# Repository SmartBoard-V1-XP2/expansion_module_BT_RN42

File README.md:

# Expansion Module: Bluetooth RN42-I/RM

## Overview
This repository hosts the design and implementation of the Bluetooth RN42-I/RM Expansion Module. The RN42 is a small form factor, low power Bluetooth 2.1 + EDR module designed for adding robust wireless capability to any device. It is perfect for mobile applications and is fully compliant with Bluetooth 2.1 + EDR standards. The module can easily be connected to a microcontroller or a processor board for Bluetooth serial communication via UART.

## Key Features of RN42
- **Bluetooth 2.1 + EDR**: Ensures compatibility with a wide range of devices and offers enhanced data rate (EDR) for faster data transfer.
- **Low Power Consumption**: Ideal for battery-powered applications with its low power consumption in sleep mode.
- **Class 2 Transmission**: Offers a reliable wireless range of up to 30 meters.
- **Easy Integration**: Supports multiple interfaces including UART, GPIOs which makes it versatile for integration into different projects.
- **Compact Size**: The module's small footprint (26.92mm x 13.21mm x 2.0mm) makes it suitable for space-constrained applications.

For more detailed information on the RN42 module, including technical specifications and usage guidelines, please refer to the [RN42 Datasheet](RN42_50002328A.pdf) available in this repository.

## Module Overview
The RN42-I/RM module is engineered for rapid integration into devices requiring wireless connectivity. It provides a high-speed interface between the device and its intended application, with minimal power consumption and robust connectivity features. The module supports secure and encrypted data transmission, ensuring that your device communicates safely over Bluetooth connections.

## Contributions and Feedback
Contributions to this project are welcome. If you have suggestions for improvement or have developed additional features, please fork the repository, make your changes, and submit a pull request. For any questions or issues, please open an issue in the GitHub repository.

## License
This project is licensed under the MIT License with the following terms:

- **Permission to Use**: You are free to use, modify, and distribute this design in both private and commercial settings.
- **Attribution Requirement**: While not required, attribution to the original author, Adam Łuczak, is appreciated. This can be done through a citation or a link back to this repository.
- **No Warranty**: This design is provided "as is", without warranty of any kind. Use it at your own risk.
- **Liability**: The author is not liable for any damages or losses that may arise from the use of this design.

For the full terms and conditions, please refer to the MIT License documentation.

## Contact
Should you have any inquiries or suggestions regarding this project, please don't hesitate to contact Adam Łuczak at adam.luczak@outlook.com.

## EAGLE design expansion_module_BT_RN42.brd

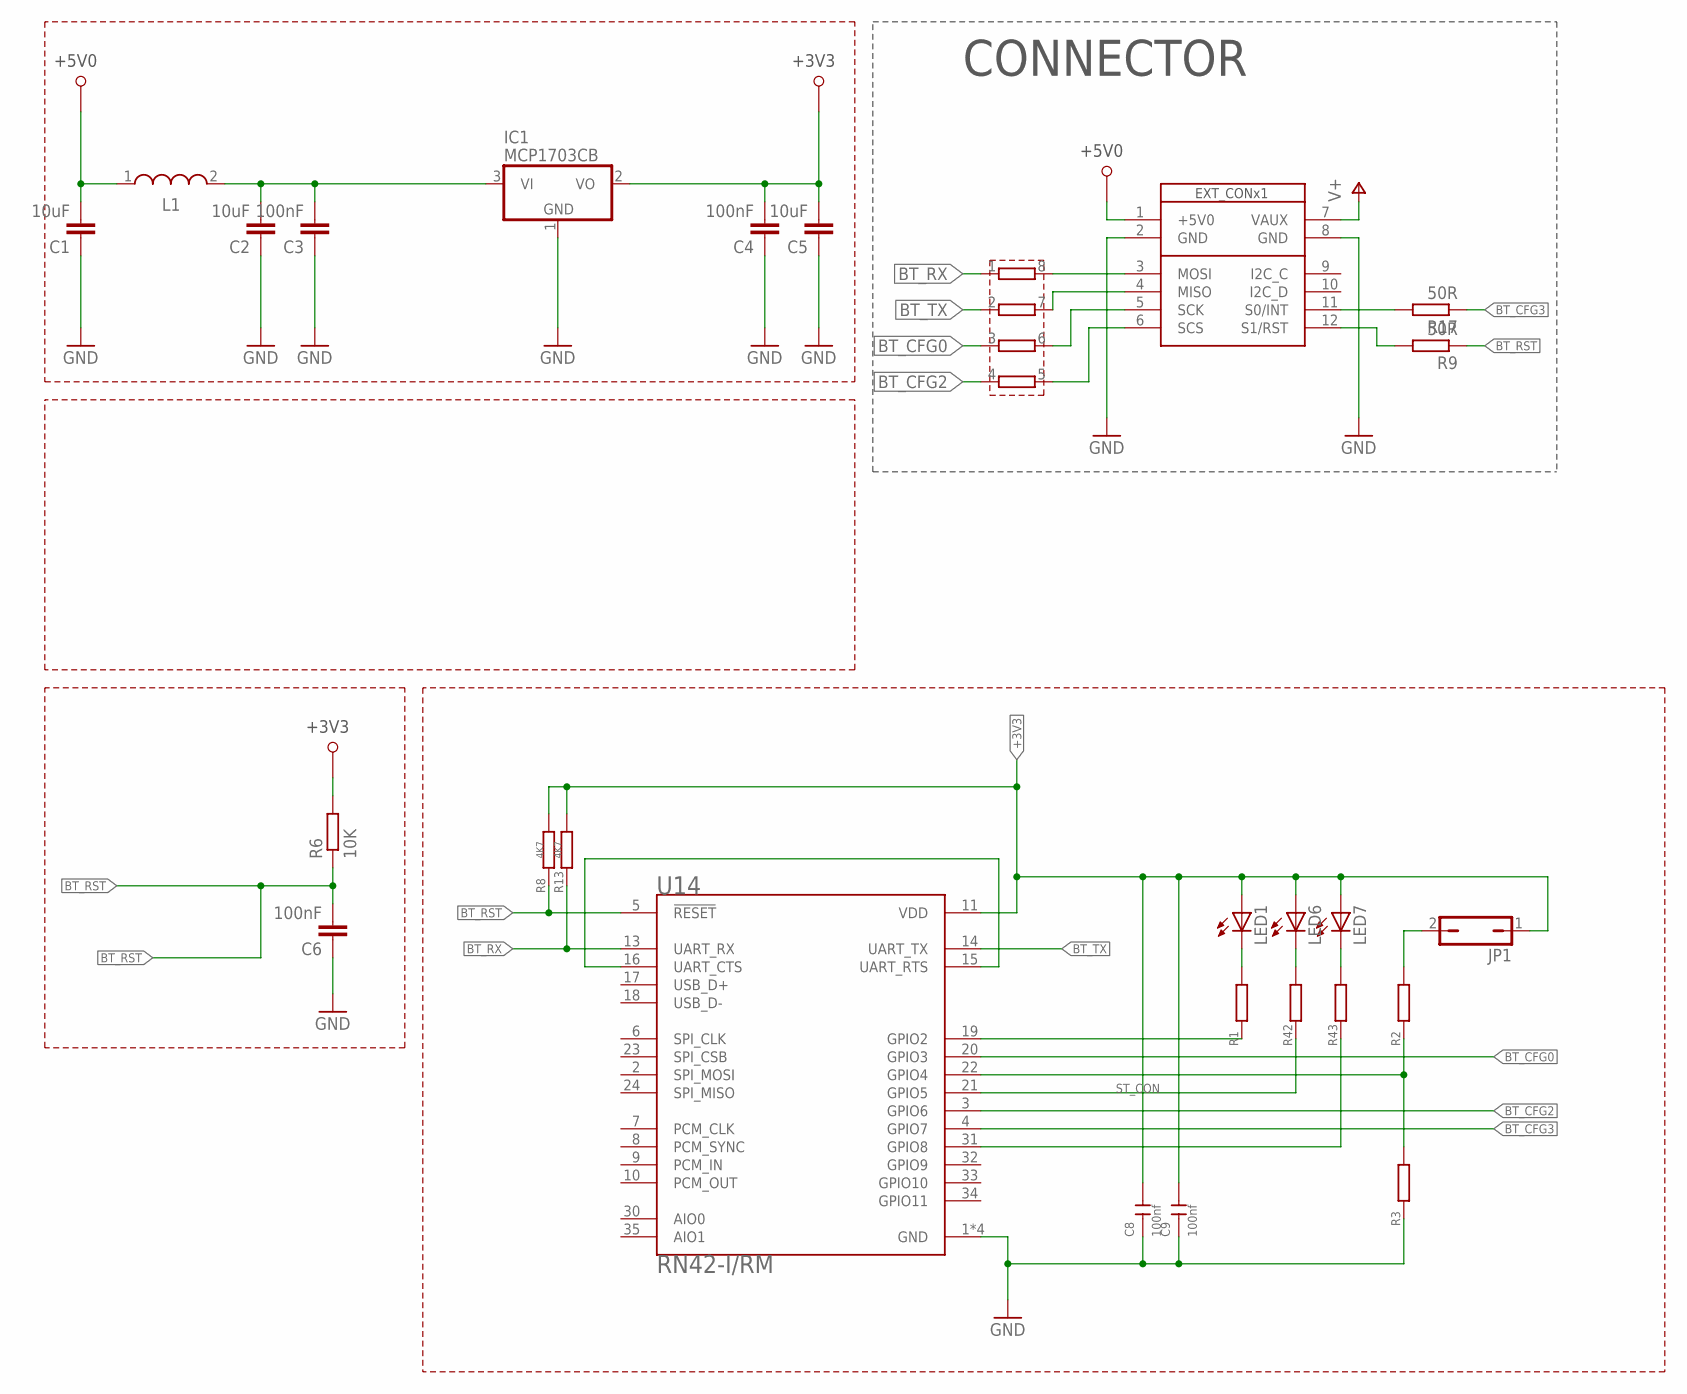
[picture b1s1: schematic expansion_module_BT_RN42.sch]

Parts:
C1, C2, C5: 10uF; C0603
C3, C4: 100nF; C0603
C6: 100nF; C0402
C8, C9: 100nf; C0402
IC1: MCP1703CB; SOT23
JP1: JP1Q; JP1
L1: WE-LQ_1210; WE-LQ_M
LED1, LED6, LED7: LEDSML0603; SML0603
R1, R2, R3, R42, R43: RESISTOR_0402; RESISITOR_0402
R6: 10K; RESISITOR_0402
R8, R13: 4K7; RESISITOR_0402
R9, R17: 50R; RESISITOR_0402
RN3: RESISTOR-DIL_4R-N; EXB28V
U14: RN42-I/RM; XCVR_RN42-I/RM
U$11: SB_EXT_CON_X1_SPI; SB_EXT_CON_X1_FULL

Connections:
+3V3: C4.2, C5.2, C8.2, C9.2, IC1.2 (VO), JP1.1, LED1.A, LED6.A, LED7.A, R6.2, R8.2, R13.2, U14.11 (VDD)
+5V0: C1.2, L1.1, U$11.1 (+5V0)
BT_CFG0: RN3.3, U14.20 (GPIO3)
BT_CFG2: RN3.4, U14.3 (GPIO6)
BT_CFG3: R17.1, U14.4 (GPIO7)
BT_CTS: U14.15 (UART_RTS), U14.16 (UART_CTS)
BT_RST: C6.2, R6.1, R8.1, R9.1, U14.5 (!RESET)
BT_RX: R13.1, RN3.1, U14.13 (UART_RX)
BT_TX: RN3.2, U14.14 (UART_TX)
GND: C1.1, C2.1, C3.1, C4.1, C5.1, C6.1, C8.1, C9.1, IC1.1 (GND), R3.1, U14.1 (GND), U14.12 (GND), U14.28 (GND), U14.29 (GND), U$11.2 (GND), U$11.8 (GND)
unnamed: C2.2, C3.2, IC1.3 (VI), L1.2
unnamed: R9.2, U$11.12 (S1/RST)
unnamed: R17.2, U$11.11 (S0/INT)
unnamed: LED1.C, R1.2
unnamed: R1.1, U14.19 (GPIO2)
unnamed: R2.1, R3.2, U14.22 (GPIO4)
unnamed: JP1.2, R2.2
unnamed: LED6.C, R42.2
unnamed: RN3.8, U$11.3 (MOSI)
unnamed: LED7.C, R43.2
unnamed: RN3.7, U$11.4 (MISO)
unnamed: RN3.6, U$11.5 (SCK)
unnamed: RN3.5, U$11.6 (SCS)
unnamed: R43.1, U14.31 (GPIO8)
ST_CON: R42.1, U14.21 (GPIO5)
V+: U$11.7 (VAUX)

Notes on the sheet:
CONNECTOR

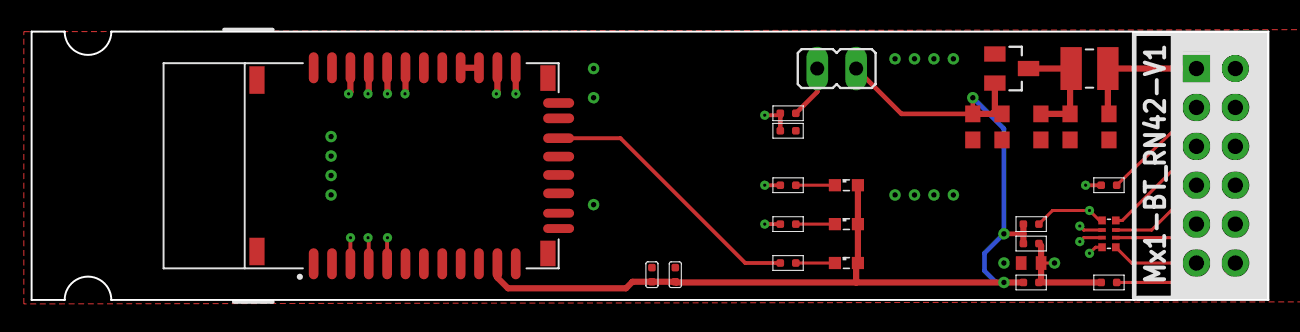
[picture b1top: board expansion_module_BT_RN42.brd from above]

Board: 4 copper layers, 80.8 x 17.5 mm, 27 parts (0 on the bottom side), 25 nets.

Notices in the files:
README.md:
License: MIT
parts and their libraries:
EagleLibrary_Wuerth_Elektronik_eiSos_rev: Copyright: Würth Elektronik
